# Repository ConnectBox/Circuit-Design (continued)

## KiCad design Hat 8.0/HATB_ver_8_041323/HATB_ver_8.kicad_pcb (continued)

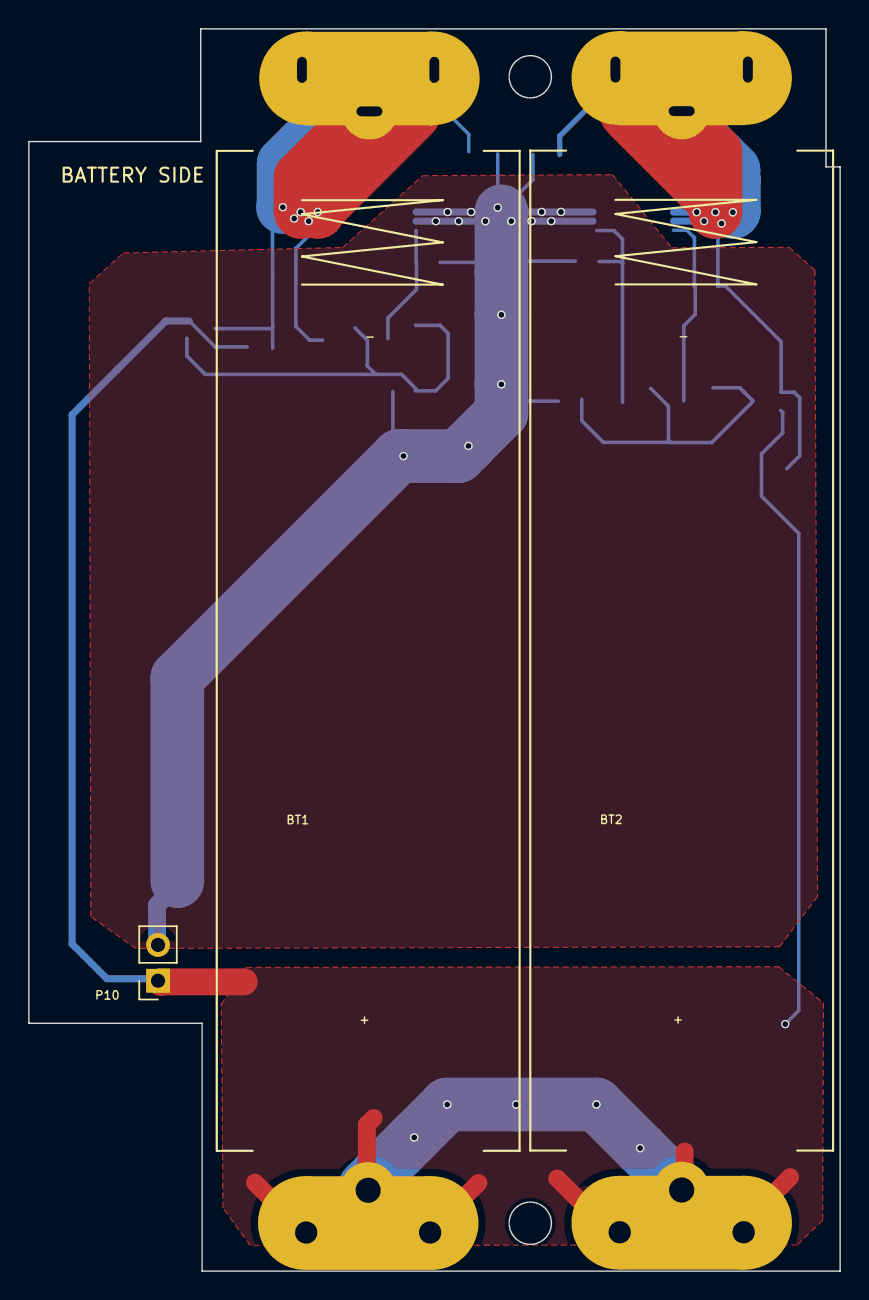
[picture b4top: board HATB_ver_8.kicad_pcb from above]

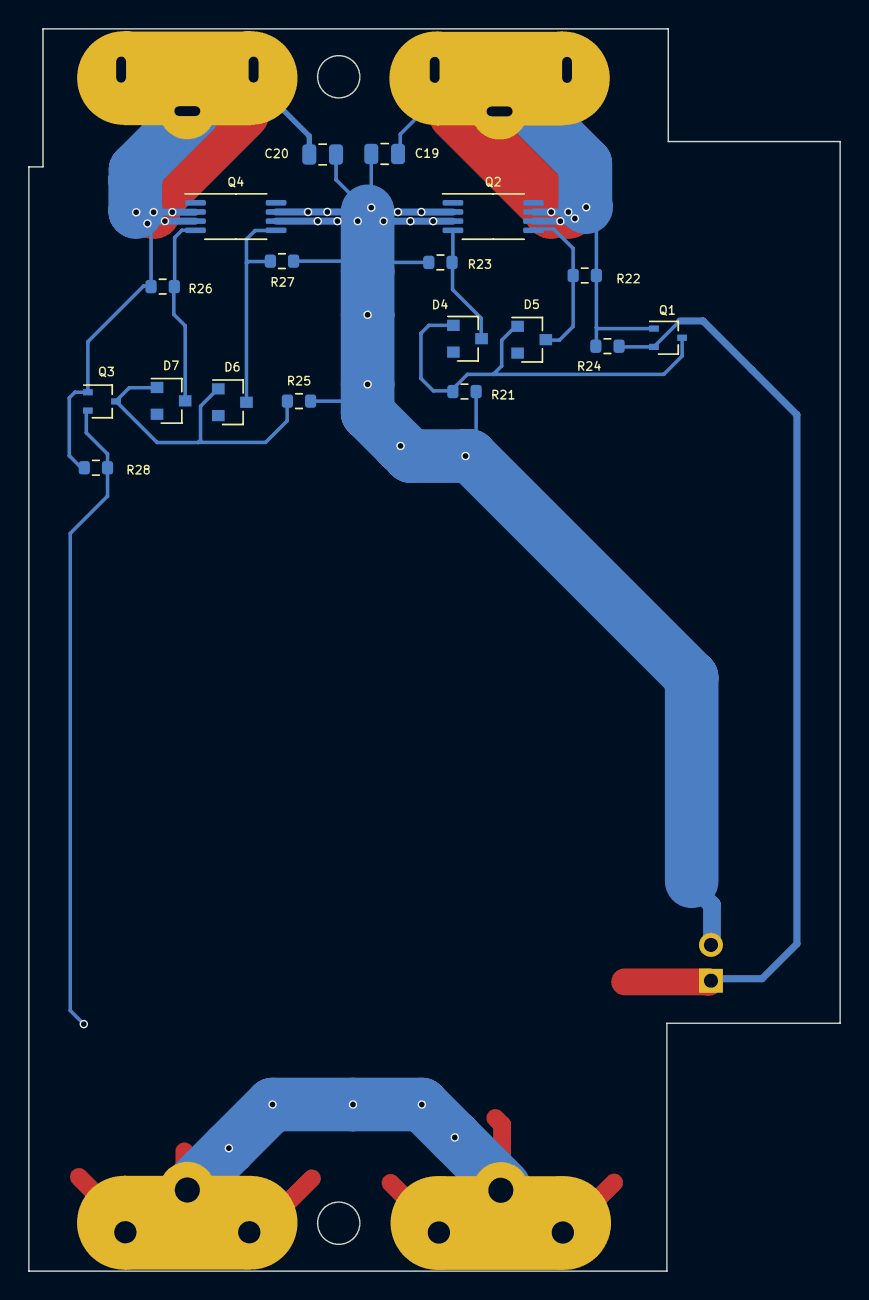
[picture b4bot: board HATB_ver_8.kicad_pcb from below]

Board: 2 copper layers, 57.6 x 88.2 mm, 21 parts (18 on the bottom side), 10 nets.

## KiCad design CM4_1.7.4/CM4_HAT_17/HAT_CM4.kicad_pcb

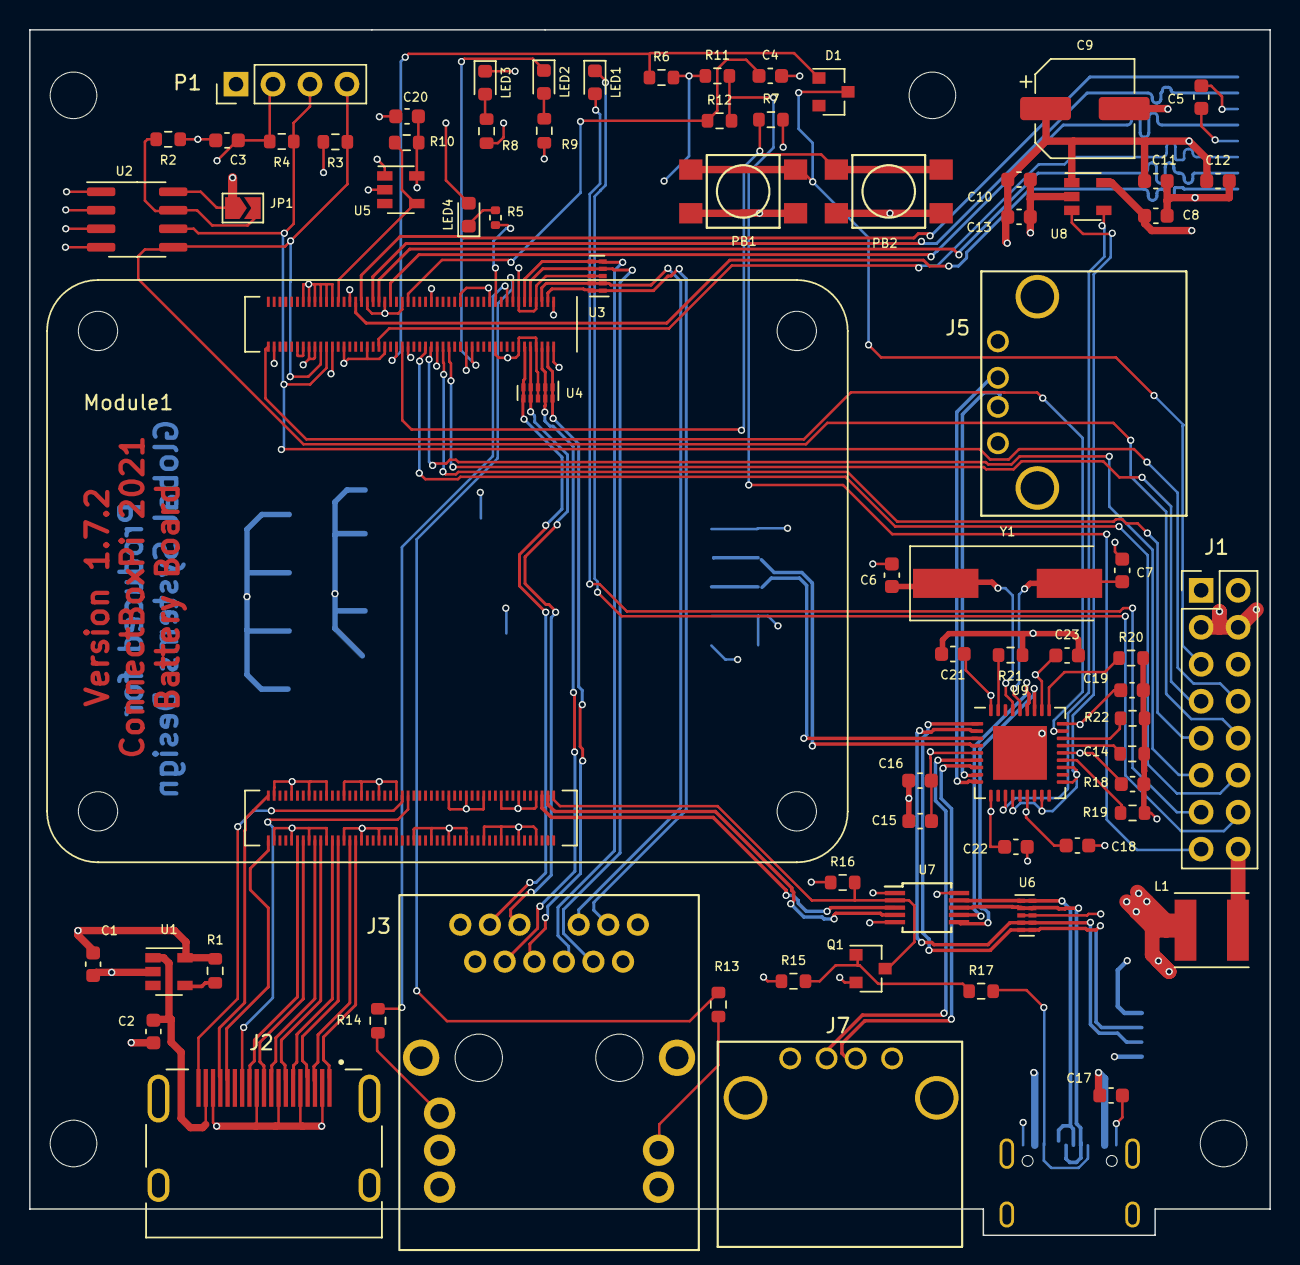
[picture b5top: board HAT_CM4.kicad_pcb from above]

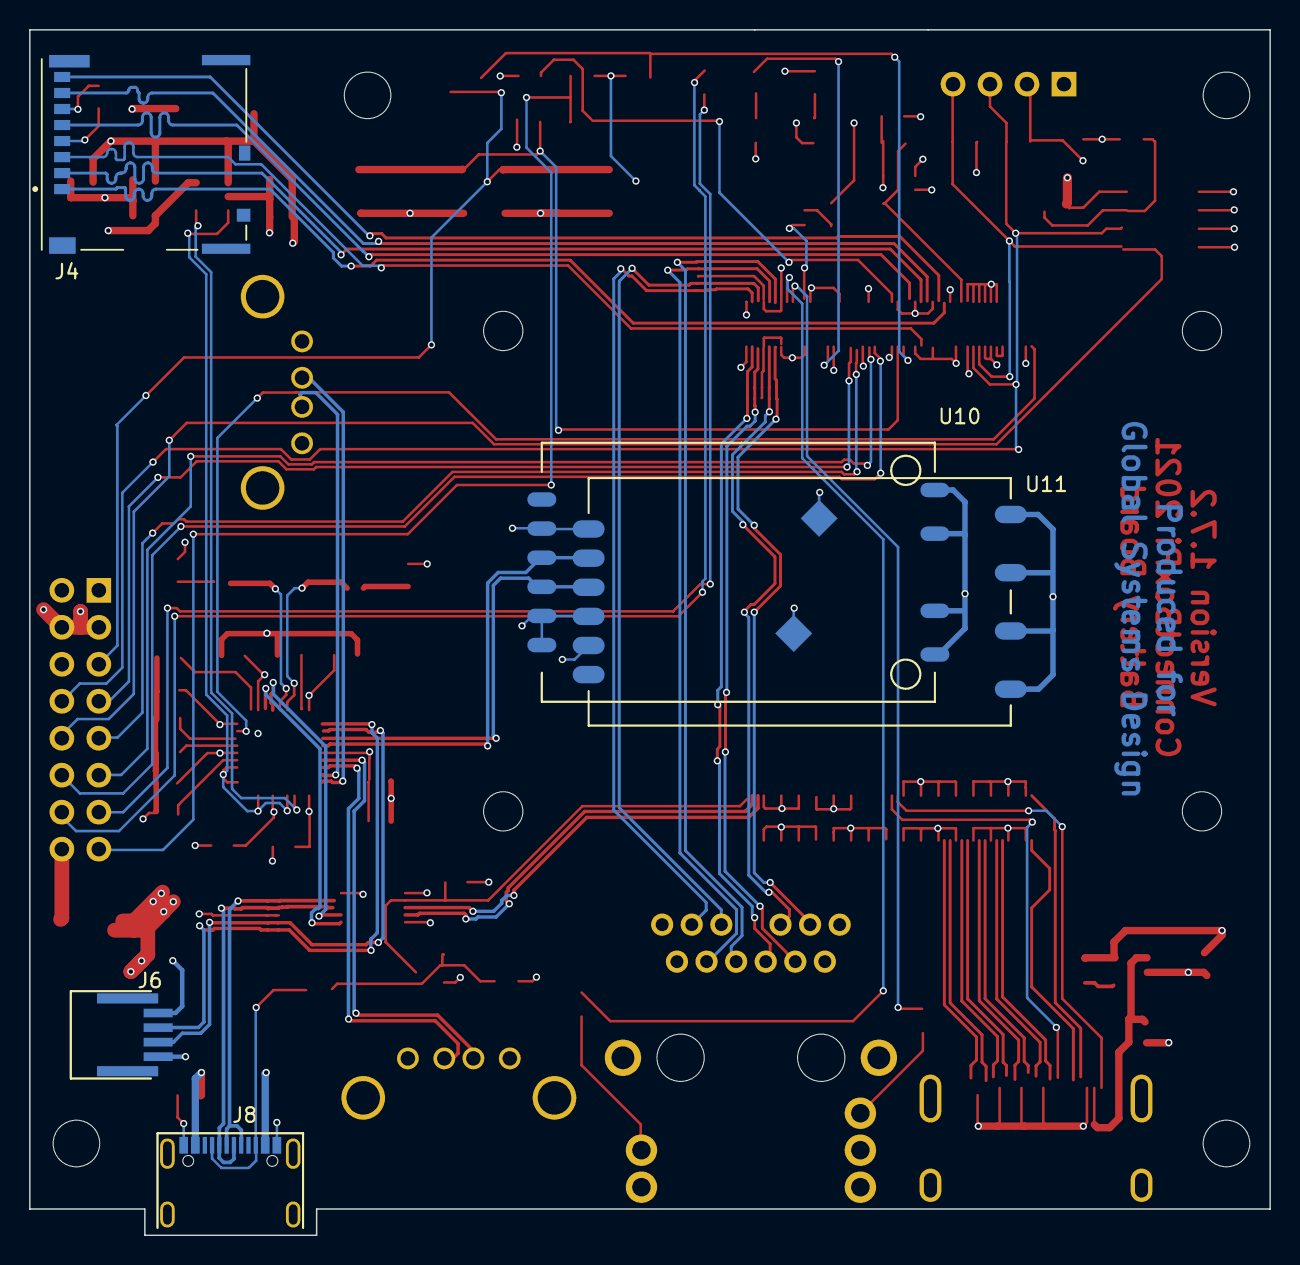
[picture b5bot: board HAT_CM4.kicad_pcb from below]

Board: 4 copper layers, 85.2 x 82.8 mm, 78 parts (5 on the bottom side), 87 nets.

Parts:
C1, C2, C16, C18, C19, C21, C22, C23: 0.1uf; C_0603_1608Metric
C3: 1uF; C_0603_1608Metric
C4, C5, C8, C10, C11, C12, C13, C14, C15: 10uF; C_0603_1608Metric
C6, C7: 27pF; C_0603_1608Metric
C9: 100uF; CP_Elec_6.3x4.5
C17, C20: 22uF; C_0603_1608Metric
D1: MMBD914; D_SOT-23_ANK
J1: Conn_02x08_Odd_Even; PinHeader_2x08_P2.54mm_Vertical
J2: 690-019-298-412; EDAC 690-019-298-412
J3: MagJack-L829-1J1T-JM; MagJack L829-1J1T-JM
J4: Micro_SD_Card; SDCARD_MOLEX_503398-1892
J5, J7: USB_A
J6: Conn_01x04; HFW4R
J8: USB-C; USB-C-GCT
JP1: SolderJumper_2_Open; SolderJumper-2_P1.3mm_Open_TrianglePad1.0x1.5mm
L1: 1.5 uH; L_Taiyo-Yuden_NR-50xx
LED1: Red; LED_0603_1608Metric
LED2: Amber; LED_0603_1608Metric
LED3: Green; LED_0603_1608Metric
LED4: LED Green; LED_0603_1608Metric
MT4: MountingHole_3.2mm_M3_ISO7380
Module1: ComputeModule4; Raspberry-Pi-4-Compute-Module
P1: Conn_01x04; PinHeader_1x04_P2.54mm_Vertical
PB1, PB2: SPST-PUSH; SW-TL3305
Q1: 2N7002; SOT-23
R1, R10, R21: 12K; R_0603_1608Metric
R2, R6, R7: 10K; R_0603_1608Metric
R3, R4, R16, R17: 2.2K; R_0603_1608Metric
R5: 1k; R_0402_1005Metric
R8, R9: 510; R_0603_1608Metric
R11, R15: 51K; R_0603_1608Metric
R12: 1K; R_0603_1608Metric
R13, R14: 470; R_0603_1608Metric
R18, R19, R20, R22: 36.0K; R_0603_1608Metric
U1, U5, U8: RT9742ANGJ5F; SOT-23-5
U2: AT24CS01-SSHM; SOIC-8_3.9x4.9mm_P1.27mm
U3, U4, U6: TPD4EUSB30; USON-10_2.5x1.0mm_P0.5mm
U7: FSUSB42MUX; MSOP-10_3x3mm_P0.5mm
U9: USB2514B-I/M2; QFN-36-1EP_6x6mm_P0.5mm_EP3.7x3.7mm
U10: HC-R8812AF1; HC-R8812AU2
U11: WG233-R8812BU
Y1: 24MHz; Crystal_SMD_HC49-SD

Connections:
+3.3v: C3.1, C14.1, C15.1, C16.1, C18.1, C19.1, C20.1, C21.1, C22.1, C23.1, J3.14 (LEDY_A), J3.16 (COM), Module1.78 (GPIO_VREF(1.8v/3.3v_Input)), Module1.84 (+3.3v_(Output)), Module1.86 (+3.3v_(Output)), P1.2, R3.2, R4.2, R6.2, R7.2, R9.1, R10.2, R11.1, R15.1, R16.1, U5.5 (VIN), U7.1 (VCC), U9.5 (VDDA33), U9.10 (VDDA33), U9.15 (VDD33), U9.23 (VDD33), U9.27 (VBUS_DET), U9.29 (VDDA33), U9.36 (VDDA33), U10.1 (PDN), U10.2 (3.3V), U11.3 (3.3V)
+5V: C1.1, C8.1, J1.3, J1.4, JP1.1 (A), LED4.2 (A), Module1.77 (+5v_(Input)), Module1.79 (+5v_(Input)), Module1.81 (+5v_(Input)), Module1.83 (+5v_(Input)), Module1.85 (+5v_(Input)), Module1.87 (+5v_(Input)), R1.2, R8.1, U1.5 (VIN), U2.8 (VCC), U8.5 (VIN)
/AC_IN: C17.1, J1.6, J8.A4/B9 (Power), J8.B4/A9 (Power)
/CHGLED_A: J1.13, LED1.2 (A)
/CHGLED_C: J1.14, LED1.1 (K)
/CM4_GPIO/+1.8v: Module1.88 (+1.8v_(Output)), Module1.90 (+1.8v_(Output))
/CM4_GPIO/ETH_LEDG: Module1.17 (Ethernet_nLED2(3.3v)), R14.1
/CM4_GPIO/ETH_LEDY: Module1.15 (Ethernet_nLED3(3.3v)), R13.1
/CM4_GPIO/GPIO6: LED2.1 (K), Module1.30 (GPIO6)
/CM4_GPIO/GPIO_IRQ: C4.1, Module1.51 (GPIO15), R12.1
/CM4_GPIO/GPIO_PB1: D1.2 (A), Module1.56 (GPIO3), R6.1
/CM4_GPIO/GPIO_PB2: Module1.54 (GPIO4), PB2.1, R7.1
/CM4_GPIO/PI_nLED_Activity: Module1.21 (PI_nLED_Activity), R5.2
/CM4_GPIO/SD_CLK: J4.5 (CLK), Module1.57 (SD_CLK)
/CM4_GPIO/SD_CMD: J4.3 (CMD), Module1.62 (SD_CMD)
/CM4_GPIO/SD_DAT0: J4.7 (DAT0), Module1.63 (SD_DAT0)
/CM4_GPIO/SD_DAT1: J4.8 (DAT1), Module1.67 (SD_DAT1)
/CM4_GPIO/SD_DAT2: J4.1 (DAT2), Module1.69 (SD_DAT2)
/CM4_GPIO/SD_DAT3: J4.2 (DAT3/CD), Module1.61 (SD_DAT3)
/CM4_GPIO/SD_PWR: C5.1, J4.4 (VDD), U5.1 (VOUT)
/CM4_GPIO/SD_PWR_ON: Module1.75 (SD_PWR_ON), R10.1, U5.4 (EN)
/CM4_GPIO/TRD0_N: J3.10 (TRD0-), Module1.10 (Ethernet_Pair0_N), U4.4 (D2+), U4.7
/CM4_GPIO/TRD0_P: J3.11 (TRD0+), Module1.12 (Ethernet_Pair0_P), U4.5 (D2-), U4.6
/CM4_GPIO/TRD1_N: J3.5 (TRD1-), Module1.6 (Ethernet_Pair1_N), U4.2 (D1-), U4.9
/CM4_GPIO/TRD1_P: J3.4 (TRD1+), Module1.4 (Ethernet_Pair1_P), U4.1 (D1+), U4.10
/CM4_GPIO/TRD2_N: J3.2 (TRD2-), Module1.9 (Ethernet_Pair2_N), U3.4 (D2+), U3.7
/CM4_GPIO/TRD2_P: J3.3 (TRD2+), Module1.11 (Ethernet_Pair2_P), U3.5 (D2-), U3.6
/CM4_GPIO/TRD3_N: J3.9 (TRD3-), Module1.5 (Ethernet_Pair3_N), U3.2 (D1-), U3.9
/CM4_GPIO/TRD3_P: J3.8 (TRD3+), Module1.3 (Ethernet_Pair3_P), U3.1 (D1+), U3.10
/CM4_HighSpeed/HDMI0_CEC: J2.13 (CEC), Module1.151 (HDMI0_CEC)
/CM4_HighSpeed/HDMI0_CK_N: J2.12 (CK-), Module1.190 (HDMI0_CLK_N)
/CM4_HighSpeed/HDMI0_CK_P: J2.10 (CK+), Module1.188 (HDMI0_CLK_P)
/CM4_HighSpeed/HDMI0_D0_N: J2.9 (D0-), Module1.184 (HDMI0_TX0_N)
/CM4_HighSpeed/HDMI0_D0_P: J2.7 (D0+), Module1.182 (HDMI0_TX0_P)
/CM4_HighSpeed/HDMI0_D1_N: J2.6 (D1-), Module1.178 (HDMI0_TX1_N)
/CM4_HighSpeed/HDMI0_D1_P: J2.4 (D1+), Module1.176 (HDMI0_TX1_P)
/CM4_HighSpeed/HDMI0_D2_N: J2.3 (D2-), Module1.172 (HDMI0_TX2_N)
/CM4_HighSpeed/HDMI0_D2_P: J2.1 (D2+), Module1.170 (HDMI0_TX2_P)
/CM4_HighSpeed/HDMI0_HOTPLUG: J2.19 (HPD/HEAC-), Module1.153 (HDMI0_HOTPLUG)
/CM4_HighSpeed/HDMI0_SCL: J2.15 (SCL), Module1.200 (HDMI0_SCL)
/CM4_HighSpeed/HDMI0_SDA: J2.16 (SDA), Module1.199 (HDMI0_SDA)
/CM4_HighSpeed/HDMI_5v: C2.1, J2.18 (+5V), U1.1 (VOUT)
/CM4_HighSpeed/USB2_N: Module1.103 (USB2_N), U7.4 (D_N)
/CM4_HighSpeed/USB2_P: Module1.105 (USB2_P), U7.3 (D_P)
/CM4_HighSpeed/USBOTG_ID: Module1.101 (USB_OTG_ID), Q1.3 (D), R16.2, U7.2 (SEL)
/I2C_SCL: J1.8, Module1.80 (SCL0), P1.3, R4.1, U2.6 (SCL)
/I2C_SDA: J1.10, Module1.82 (SDA0), P1.4, R3.1, U2.5 (SDA)
/MISO: J1.9, Module1.40 (GPIO9)
/MOSI: J1.11, Module1.44 (GPIO10)
/PWR_ENA: J1.15, R11.2, R12.2
/PWR_GND: J1.16, L1.1
/PowerSwitch: D1.1 (K), J1.5, PB1.1
/SCL: J1.7, Module1.38 (GPIO11)
/USB Hub/HD1_N: J6.2, U6.5 (D2-), U6.6, U9.1 (USBDM_DN1/PRT_DIS_M1)
/USB Hub/HD1_P: J6.3, U6.4 (D2+), U6.7, U9.2 (USBDP_DN1/PRT_DIS_P1)
/USB Hub/HD2_N: U9.3 (USBDM_DN2/PRT_DIS_M2), U10.3 (DM-), U11.4 (USB_D-)
/USB Hub/HD2_P: U9.4 (USBDP_DN2/PRT_DIS_P2), U10.4 (DP+), U11.5 (USB_D+)
/USB Hub/HD3_N: J7.2 (D-), U9.6 (USBDM_DN3/PRT_DIS_M3)
/USB Hub/HD3_P: J7.3 (D+), U9.7 (USBDP_DN3/PRT_DIS_P3)
/USB Hub/HD4_N: J5.2 (D-), U9.8 (USBDM_DN4/PRT_DIS_M4)
/USB Hub/HD4_P: J5.3 (D+), U9.9 (USBDP_DN4/PRT_DIS_P4)
/USB Hub/OTG_D+: J8.A6 (D+), J8.B6 (D+), U6.1 (D1+), U6.10, U7.9 (HSD1_P)
/USB Hub/OTG_D-: J8.A7 (D-), J8.B7 (D-), U6.2 (D1-), U6.9, U7.8 (HSD1_M)
/USB Hub/OTG_ID: J8.A5 (CC1), J8.B5 (CC2), R17.2
/USB Hub/PWR1: U8.4 (EN), U9.12 (PRTPWR1/BC_EN1)
/USB Hub/USBH_N: U7.6 (HSD0_M), U9.30 (USBDM_UP)
/USB Hub/USBH_P: U7.7 (HSD0_P), U9.31 (USBDP_UP)
/USB Hub/VBUS: C9.1, C10.1, C11.1, C12.1, C13.1, J5.1 (VBUS), J6.1, J7.1 (VBUS), U8.1 (VOUT)
/USB Hub/nEXTRST: Module1.100 (nEXTRST), U9.26 (RESET_N)
/USB Hub/nOCS1: U8.3 (/FLG), U9.13 (OCS_N1), U9.17 (OCS_N2), U9.19 (OCS_N3), U9.21 (OCS_N4)
//RESET: J1.12, Module1.46 (GPIO22)
GND: C1.2, C2.2, C3.2, C4.2, C5.2, C6.2, C7.2, C8.2, C9.2, C10.2, C11.2, C12.2, C13.2, C14.2, C15.2, C16.2, C17.2, C18.2, C19.2, C20.2, C21.2, C22.2, C23.2, J1.1, J1.2, J2.2 (D2S), J2.5 (D1S), J2.8 (D0S), J2.11 (CKS), J2.17 (GND), J2.SH1 (SH), J2.SH2 (SH), J2.SH3 (SH), J2.SH4 (SH), J3.18 (SHIELD), J4.6 (VSS), J5.4 (GND), J5.5 (Shield), J6.4, J7.4 (GND), J7.5 (Shield), J8.1 (Shell), J8.A1/B12 (GND), J8.B1/A12 (GND), L1.2, LED3.1 (K), Module1.1 (GND), Module1.2 (GND), Module1.7 (GND), Module1.8 (GND), Module1.13 (GND), Module1.14 (GND), Module1.22 (GND), Module1.23 (GND), Module1.32 (GND), Module1.33 (GND), Module1.42 (GND), Module1.43 (GND), Module1.52 (GND), Module1.53 (GND), Module1.59 (GND), Module1.60 (GND), Module1.65 (GND), Module1.66 (GND), Module1.71 (GND), Module1.74 (GND), Module1.98 (GND), Module1.107 (GND), Module1.108 (GND), Module1.113 (GND), Module1.114 (GND), Module1.119 (GND), Module1.120 (GND), Module1.125 (GND), Module1.126 (GND), Module1.131 (GND), Module1.132 (GND), Module1.137 (GND), Module1.138 (GND), Module1.144 (GND), Module1.150 (GND), Module1.155 (GND), Module1.156 (GND), Module1.161 (GND), Module1.162 (GND), Module1.167 (GND), Module1.168 (GND), Module1.173 (GND), Module1.174 (GND), Module1.179 (GND), Module1.180 (GND), Module1.185 (GND), Module1.186 (GND), Module1.191 (GND), Module1.192 (GND), Module1.197 (GND), Module1.198 (GND), P1.1, PB1.2, PB2.2, Q1.2 (S), R2.1, R18.2, R19.2, R20.2, R21.1, R22.2, U1.2 (GND), U2.1 (A0), U2.2 (A1), U2.3 (A2), U2.4 (GND), U3.3 (GND), U3.8 (GND), U4.3 (GND), U4.8 (GND), U5.2 (GND), U6.3 (GND), U6.8 (GND), U7.5 (GND), U7.10 (nOE), U8.2 (GND), U9.37 (VSS), U10.5 (GND), U10.7 (GND), U10.9 (GND), U10.10 (GND), U10.12 (GND), U10.14 (GND), U10.15 (GND), U11.2 (GND), U11.6 (GND), U11.7 (GND), U11.9 (GND), U11.10 (GND), U11.12 (GND)
unnamed: C6.1, U9.33 (XTALIN/CLKIN), Y1.1
unnamed: C7.1, U9.32 (XTALOUT), Y1.2
unnamed: J3.13 (LEDY_K), R13.2
unnamed: J3.15 (LEDG_K), R14.2
unnamed: JP1.2 (B), R2.2, U2.7 (WP)
unnamed: LED2.2 (A), R9.2
unnamed: LED3.2 (A), R8.2
unnamed: LED4.1 (K), R5.1
unnamed: Q1.1 (G), R15.2, R17.1
unnamed: R1.1, U1.4 (EN)
unnamed: R18.1, U9.24 (SCL/SMBCLK/CFG_SEL0)
unnamed: R19.1, U9.22 (SDA/SMBDATA/NON_REM1)
unnamed: R20.1, U9.28 (SUSP_IND/LOCAL_PWR/NON_REM0)
unnamed: R21.2, U9.35 (RBIAS)
unnamed: R22.1, U9.25 (HS_IND/CFG_SEL1)

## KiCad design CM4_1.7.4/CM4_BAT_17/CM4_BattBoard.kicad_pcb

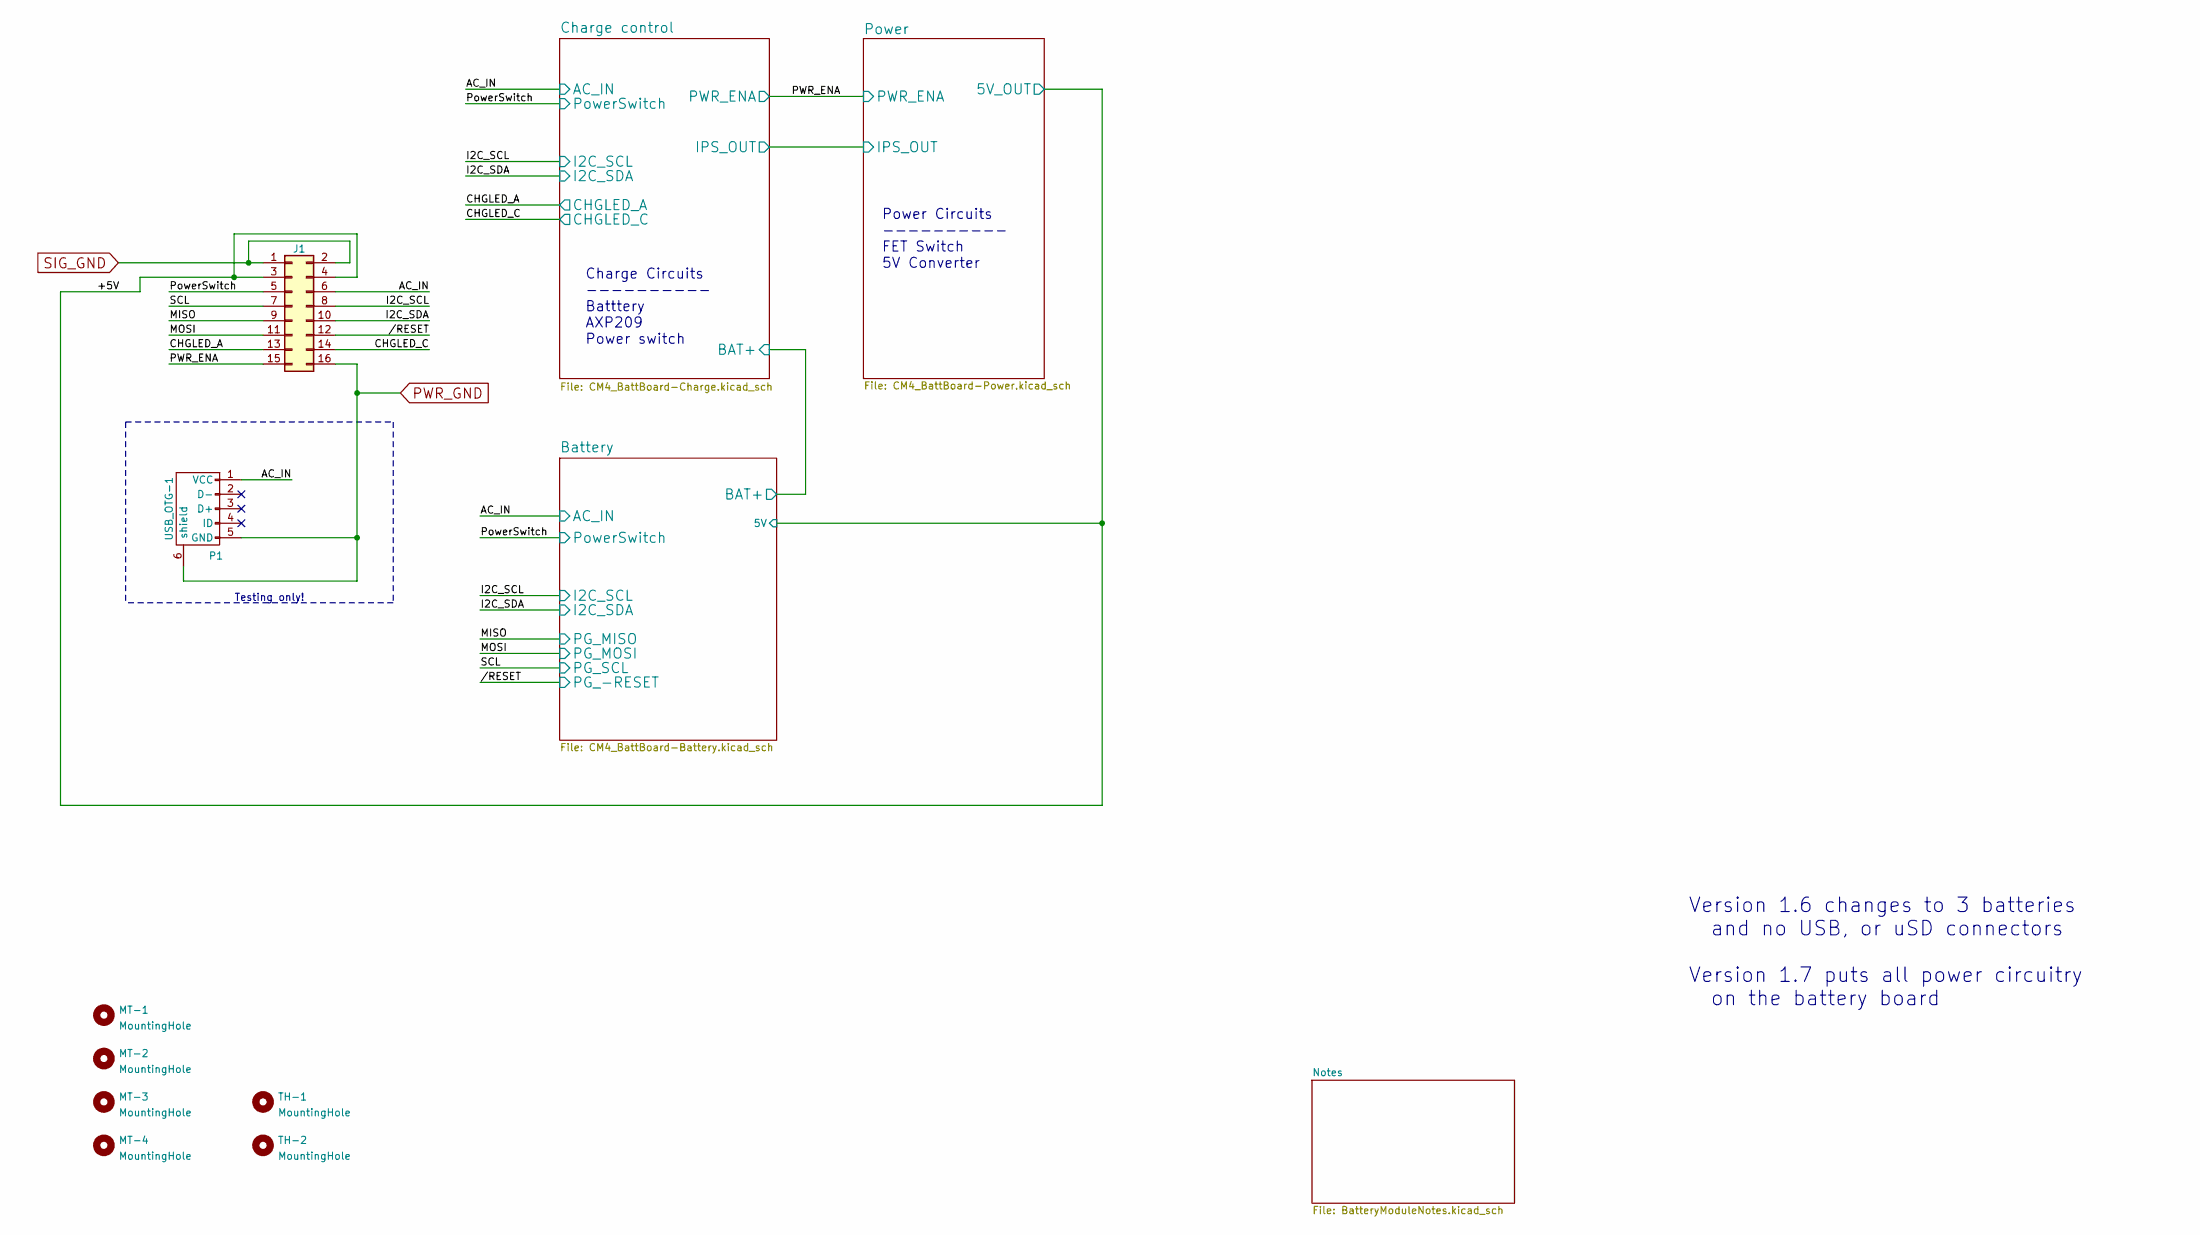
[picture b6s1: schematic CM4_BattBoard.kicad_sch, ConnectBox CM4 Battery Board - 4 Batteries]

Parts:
J1: Conn_02x08_Odd_Even; PinSocket_2x08_P2.54mm_Vertical; Manufacturer P/N PPPC082LFBN-RC; DigiKey P/N S7111-ND
MT-1, MT-2, MT-3, MT-4: MountingHole; MountingHole_2.7mm_M2.5
P1: USB_OTG-1; USB_Micro-B-TH-mount; Manufacturer P/N 10118194-0001LF; DigiKey P/N 609-4618-1-ND
TH-1, TH-2: MountingHole; MountingHole_3.2mm_M3_ISO7380

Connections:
/+5V: J1.3, J1.4; also elsewhere on the board
/AC_IN: J1.6, P1.1 (VCC); also elsewhere on the board
/CHGLED_A: J1.13; also elsewhere on the board
/CHGLED_C: J1.14; also elsewhere on the board
/I2C_SCL: J1.8; also elsewhere on the board
/I2C_SDA: J1.10; also elsewhere on the board
/MISO: J1.9; also elsewhere on the board
/MOSI: J1.11; also elsewhere on the board
/PWR_ENA: J1.15; also elsewhere on the board
/PowerSwitch: J1.5; also elsewhere on the board
/SCL: J1.7; also elsewhere on the board
//RESET: J1.12; also elsewhere on the board
PWR_GND: J1.16, P1.5 (GND), P1.6 (shield); also elsewhere on the board
SIG_GND: J1.1, J1.2; also elsewhere on the board

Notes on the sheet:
Testing only!
Charge Circuits ---------- Batttery AXP209 Power switch
Power Circuits ---------- FET Switch 5V Converter
Version 1.6 changes to 3 batteries and no USB, or uSD connectors Version 1.7 puts all power circuitry on the battery board

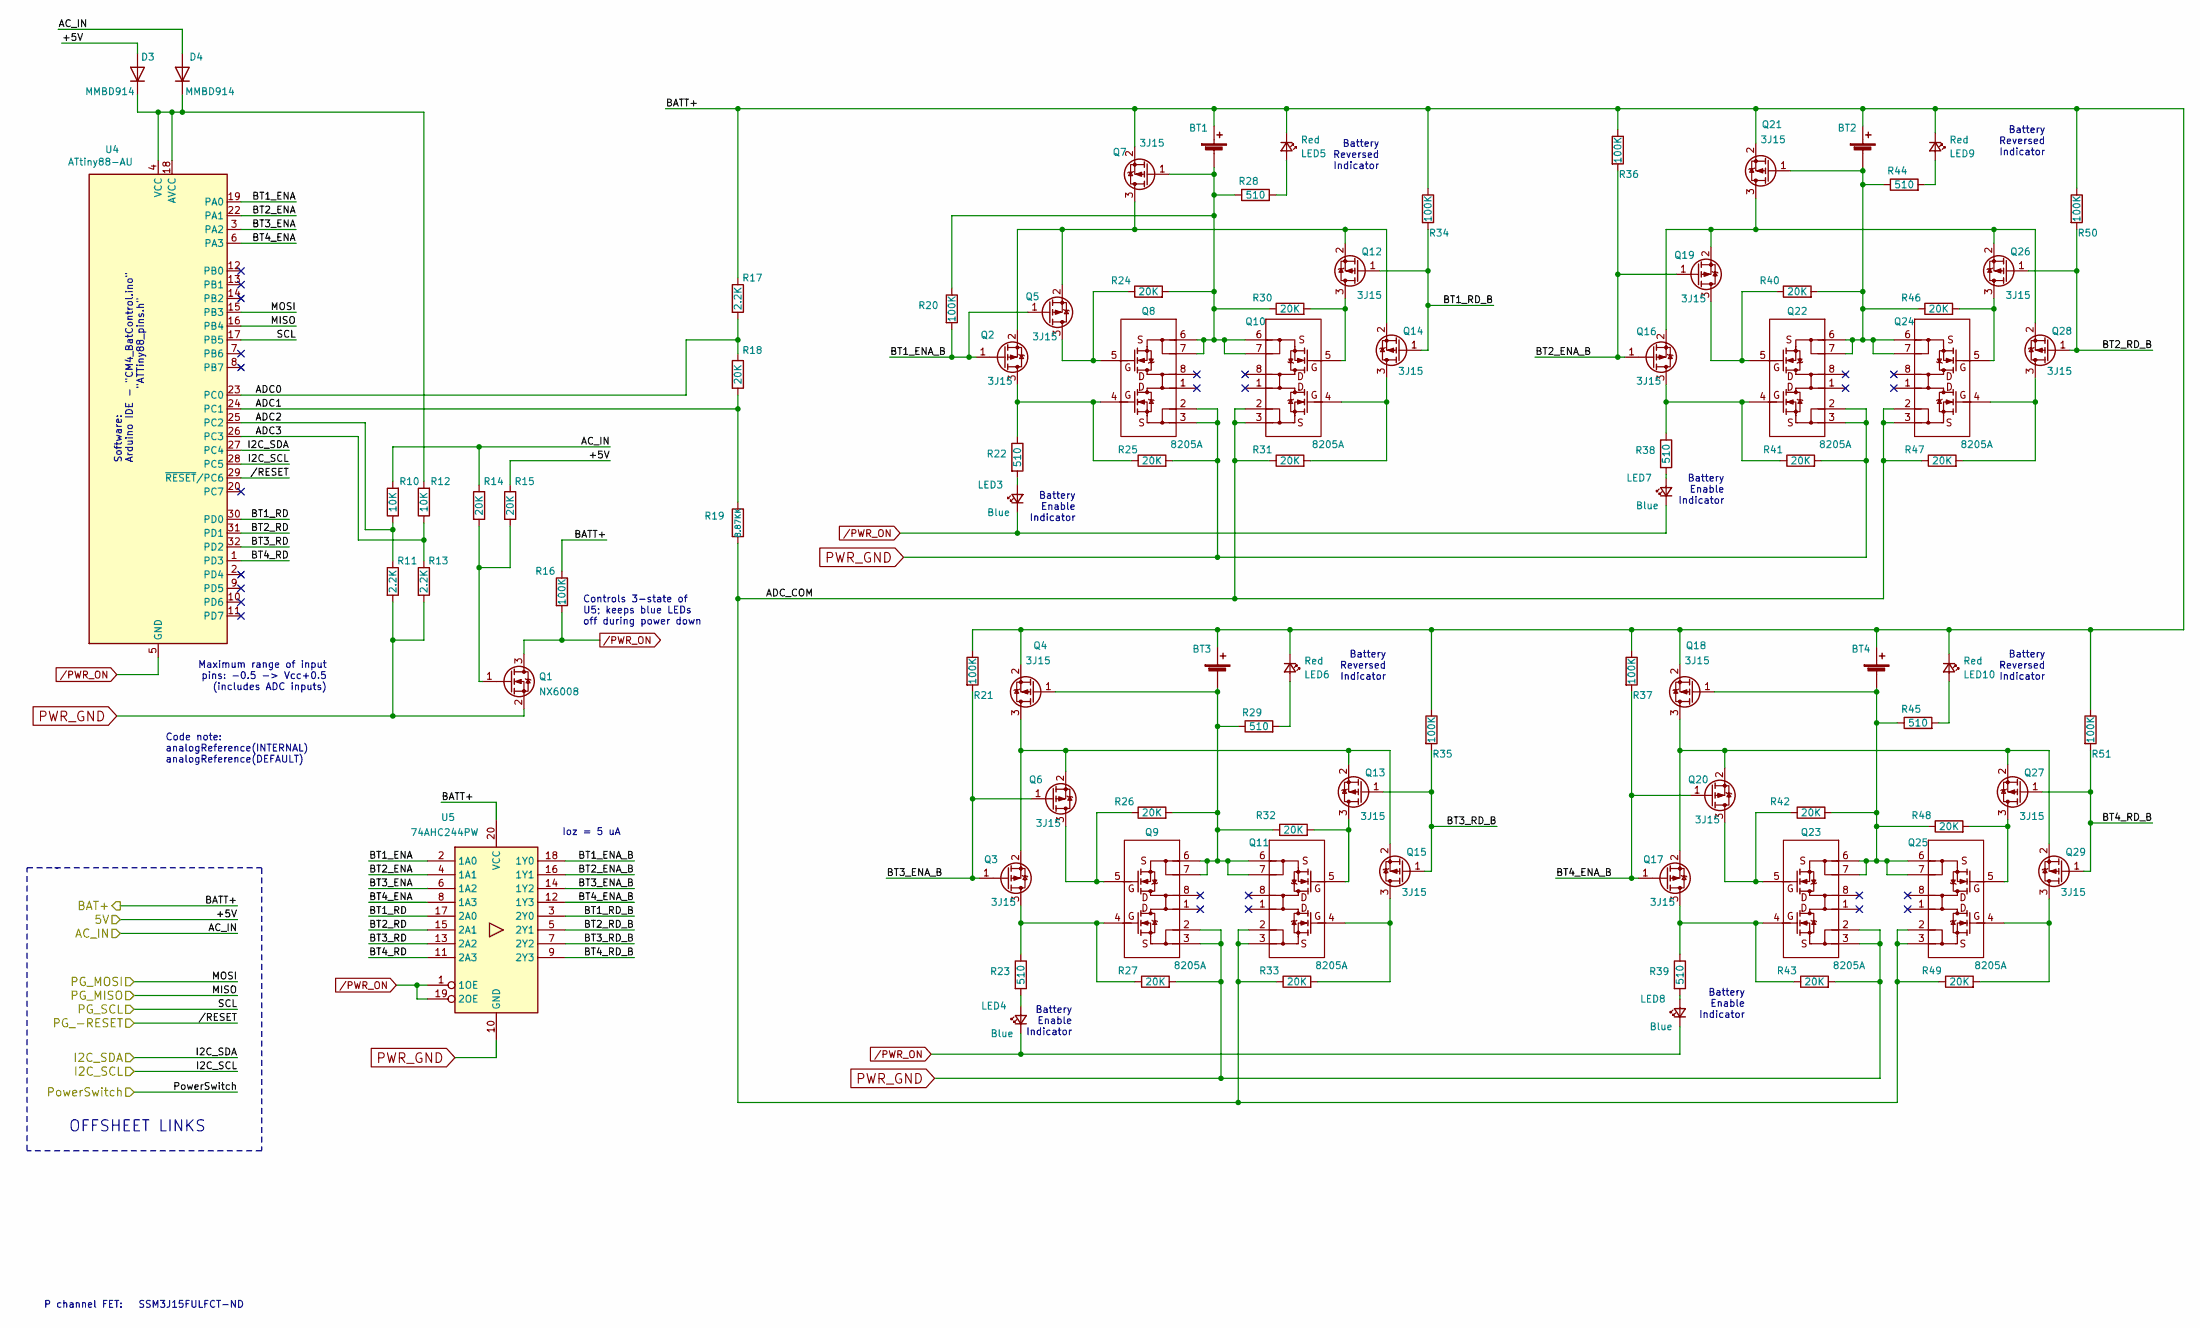
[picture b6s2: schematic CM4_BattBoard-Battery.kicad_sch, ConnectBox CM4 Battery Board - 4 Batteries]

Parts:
BT1, BT2, BT3, BT4: Battery Connector; Battery 18650-2; Manufacturer P/N 590 & 628; DigiKey P/N 36-590-ND & 36-628-ND
D3, D4: MMBD914; D_SOT-23_ANK; Manufacturer P/N MMBD914LT1G; DigiKey P/N MMBD914LT1GOSCT-ND
LED3, LED4, LED7, LED8: Blue; LED_0603_1608Metric; Manufacturer P/N IN-S63BT5B; DigiKey P/N 1830-1068-1-ND
LED5, LED6, LED9, LED10: Red; LED_0603_1608Metric; Manufacturer P/N LTST-C191KRKT; DigiKey P/N 160-1447-1-ND
Q1: NX6008; SOT-23; Manufacturer P/N NX6008NBKR; DigiKey P/N 1727-NX6008NBKRCT-ND
Q2, Q3, Q4, Q5, Q6, Q7, Q12, Q13, Q14, Q15, Q16, Q17, Q18, Q19, Q20, Q21, Q26, Q27, Q28, Q29: 3J15; SOT-323_SC-70; Manufacturer P/N SSM3J15FU,LF; DigiKey P/N SSM3J15FULFCT-ND
Q8, Q9, Q10, Q11, Q22, Q23, Q24, Q25: 8205A; TSSOP-8_4.4x3mm_P0.65mm
R10, R12: 10K; R_0603_1608Metric; Manufacturer P/N RC0603FR-0710KL; DigiKey P/N 311-10.0KHRCT-ND
R11, R13, R17: 2.2K; R_0603_1608Metric; Manufacturer P/N RC0603FR-072K2L; DigiKey P/N 311-2K2HRCT-ND
R14, R15, R18, R24, R25, R26, R27, R30, R31, R32, R33, R40, R41, R42, R43, R46, R47, R48, R49: 20K; R_0603_1608Metric; Manufacturer P/N RC0603FR-0720KL; DigiKey P/N 311-20.0KHRCT-ND
R16, R20, R21, R34, R35, R36, R37, R50, R51: 100K; R_0603_1608Metric; Manufacturer P/N RC0603FR-07100KL; DigiKey P/N 311-100KHRCT-ND
R19: 8.87KK; R_0603_1608Metric; Manufacturer P/N RC0603FR-138K87L; DigiKey P/N 13-RC0603FR-138K87LCT-ND
R22, R23, R28, R29, R38, R39, R44, R45: 510; R_0603_1608Metric; Manufacturer P/N RC0603FR-07510RL; DigiKey P/N 311-510RHRCT-ND
U4: ATtiny88-AU; TQFP-32_7x7mm_P0.8mm; Manufacturer P/N ATTINY88-AU; DigiKey P/N ATTINY88-AU-ND
U5: 74AHC244PW; TSSOP-20_4.4x6.5mm_P0.65mm; Manufacturer P/N 74AHC244PW,118; DigiKey P/N 296-1097-1-ND

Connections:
/+5V: D3.2 (A), R15.1; also elsewhere on the board
/AC_IN: D4.2 (A), R10.2, R14.1; also elsewhere on the board
/Battery/ADC1: R18.2, R19.1, U4.24 (PC1)
/Battery/ADC2: R10.1, R11.1, U4.25 (PC2)
/Battery/ADC3: R12.1, R13.1, U4.26 (PC3)
/Battery/ADC_COM: Q10.2 (S1), Q10.3 (S1), Q11.2 (S1), Q11.3 (S1), Q24.2 (S1), Q24.3 (S1), Q25.2 (S1), Q25.3 (S1), R19.2, R31.1, R33.1, R47.1, R49.1
/Battery/BT1_ENA: U4.19 (PA0), U5.2 (1A0)
/Battery/BT1_ENA_B: Q2.1 (G), Q5.1 (G), R20.2, U5.18 (1Y0)
/Battery/BT1_RD: U4.30 (PD0), U5.17 (2A0)
/Battery/BT1_RD_B: Q12.1 (G), Q14.1 (G), R34.2, U5.3 (2Y0)
/Battery/BT2_ENA: U4.22 (PA1), U5.4 (1A1)
/Battery/BT2_ENA_B: Q16.1 (G), Q19.1 (G), R36.2, U5.16 (1Y1)
/Battery/BT2_RD: U4.31 (PD1), U5.15 (2A1)
/Battery/BT2_RD_B: Q26.1 (G), Q28.1 (G), R50.2, U5.5 (2Y1)
/Battery/BT3_ENA: U4.3 (PA2), U5.6 (1A2)
/Battery/BT3_ENA_B: Q3.1 (G), Q6.1 (G), R21.2, U5.14 (1Y2)
/Battery/BT3_RD: U4.32 (PD2), U5.13 (2A2)
/Battery/BT3_RD_B: Q13.1 (G), Q15.1 (G), R35.2, U5.7 (2Y2)
/Battery/BT4_ENA: U4.6 (PA3), U5.8 (1A3)
/Battery/BT4_ENA_B: Q17.1 (G), Q20.1 (G), R37.2, U5.12 (1Y3)
/Battery/BT4_RD: U4.1 (PD3), U5.11 (2A3)
/Battery/BT4_RD_B: Q27.1 (G), Q29.1 (G), R51.2, U5.9 (2Y3)
/I2C_SCL: U4.28 (PC5); also elsewhere on the board
/I2C_SDA: U4.27 (PC4); also elsewhere on the board
/MISO: U4.16 (PB4); also elsewhere on the board
/MOSI: U4.15 (PB3); also elsewhere on the board
/SCL: U4.17 (PB5); also elsewhere on the board
//RESET: U4.29 (~RESET/PC6); also elsewhere on the board
unnamed: BT1.2 (-), Q7.1 (G), Q8.6 (S2), Q8.7 (S2), Q10.6 (S2), Q10.7 (S2), R20.1, R24.2, R28.1, R30.1
unnamed: D3.1 (K), D4.1 (K), R12.2, U4.4 (VCC), U4.18 (AVCC)
unnamed: LED3.2 (A), R22.2
unnamed: LED4.2 (A), R23.2
unnamed: LED5.2 (A), R28.2
unnamed: LED6.2 (A), R29.2
unnamed: LED7.2 (A), R38.2
unnamed: LED8.2 (A), R39.2
unnamed: LED9.2 (A), R44.2
unnamed: LED10.2 (A), R45.2
unnamed: Q1.1 (G), R14.2, R15.2
unnamed: Q2.3 (D), Q8.4 (G1), R22.1, R25.1
unnamed: Q3.3 (D), Q9.4 (G1), R23.1, R27.1
unnamed: Q5.3 (D), Q8.5 (G2), R24.1
unnamed: Q6.3 (D), Q9.5 (G2), R26.1
unnamed: Q10.4 (G1), Q14.3 (D), R31.2
unnamed: Q10.5 (G2), Q12.3 (D), R30.2
unnamed: Q11.4 (G1), Q15.3 (D), R33.2
unnamed: Q11.5 (G2), Q13.3 (D), R32.2
unnamed: BT3.2 (-), Q4.1 (G), Q9.6 (S2), Q9.7 (S2), Q11.6 (S2), Q11.7 (S2), R26.2, R29.1, R32.1
unnamed: Q2.2 (S), Q5.2 (S), Q7.3 (D), Q12.2 (S), Q14.2 (S)
unnamed: Q3.2 (S), Q4.3 (D), Q6.2 (S), Q13.2 (S), Q15.2 (S)
unnamed: Q16.2 (S), Q19.2 (S), Q21.3 (D), Q26.2 (S), Q28.2 (S)
unnamed: Q16.3 (D), Q22.4 (G1), R38.1, R41.1
unnamed: Q17.2 (S), Q18.3 (D), Q20.2 (S), Q27.2 (S), Q29.2 (S)
unnamed: Q17.3 (D), Q23.4 (G1), R39.1, R43.1
unnamed: BT4.2 (-), Q18.1 (G), Q23.6 (S2), Q23.7 (S2), Q25.6 (S2), Q25.7 (S2), R42.2, R45.1, R48.1
unnamed: Q19.3 (D), Q22.5 (G2), R40.1
unnamed: Q20.3 (D), Q23.5 (G2), R42.1
unnamed: BT2.2 (-), Q21.1 (G), Q22.6 (S2), Q22.7 (S2), Q24.6 (S2), Q24.7 (S2), R40.2, R44.1, R46.1
unnamed: Q24.4 (G1), Q28.3 (D), R47.2
unnamed: Q24.5 (G2), Q26.3 (D), R46.2
unnamed: Q25.4 (G1), Q29.3 (D), R49.2
unnamed: Q25.5 (G2), Q27.3 (D), R48.2
PWR_GND: Q1.2 (S), Q8.2 (S1), Q8.3 (S1), Q9.2 (S1), Q9.3 (S1), Q22.2 (S1), Q22.3 (S1), Q23.2 (S1), Q23.3 (S1), R11.2, R13.2, R25.2, R27.2, R41.2, R43.2, U5.10 (GND); also elsewhere on the board
/PWR_ON: LED3.1 (K), LED4.1 (K), LED7.1 (K), LED8.1 (K), Q1.3 (D), R16.2, U4.5 (GND), U4.21 (GND), U5.1 (1OE), U5.19 (2OE)

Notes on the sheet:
OFFSHEET LINKS
Software: Arduino IDE - "CM4_BatControl.ino" "ATTiny88_pins.h"
Code note: analogReference(INTERNAL) analogReference(DEFAULT)
P channel FET: SSM3J15FULFCT-ND
Maximum range of input pins: -0.5 -> Vcc+0.5 (includes ADC inputs)
Ioz = 5 uA
Controls 3-state of U5; keeps blue LEDs off during power down
Battery Enable Indicator
Battery Reversed Indicator
